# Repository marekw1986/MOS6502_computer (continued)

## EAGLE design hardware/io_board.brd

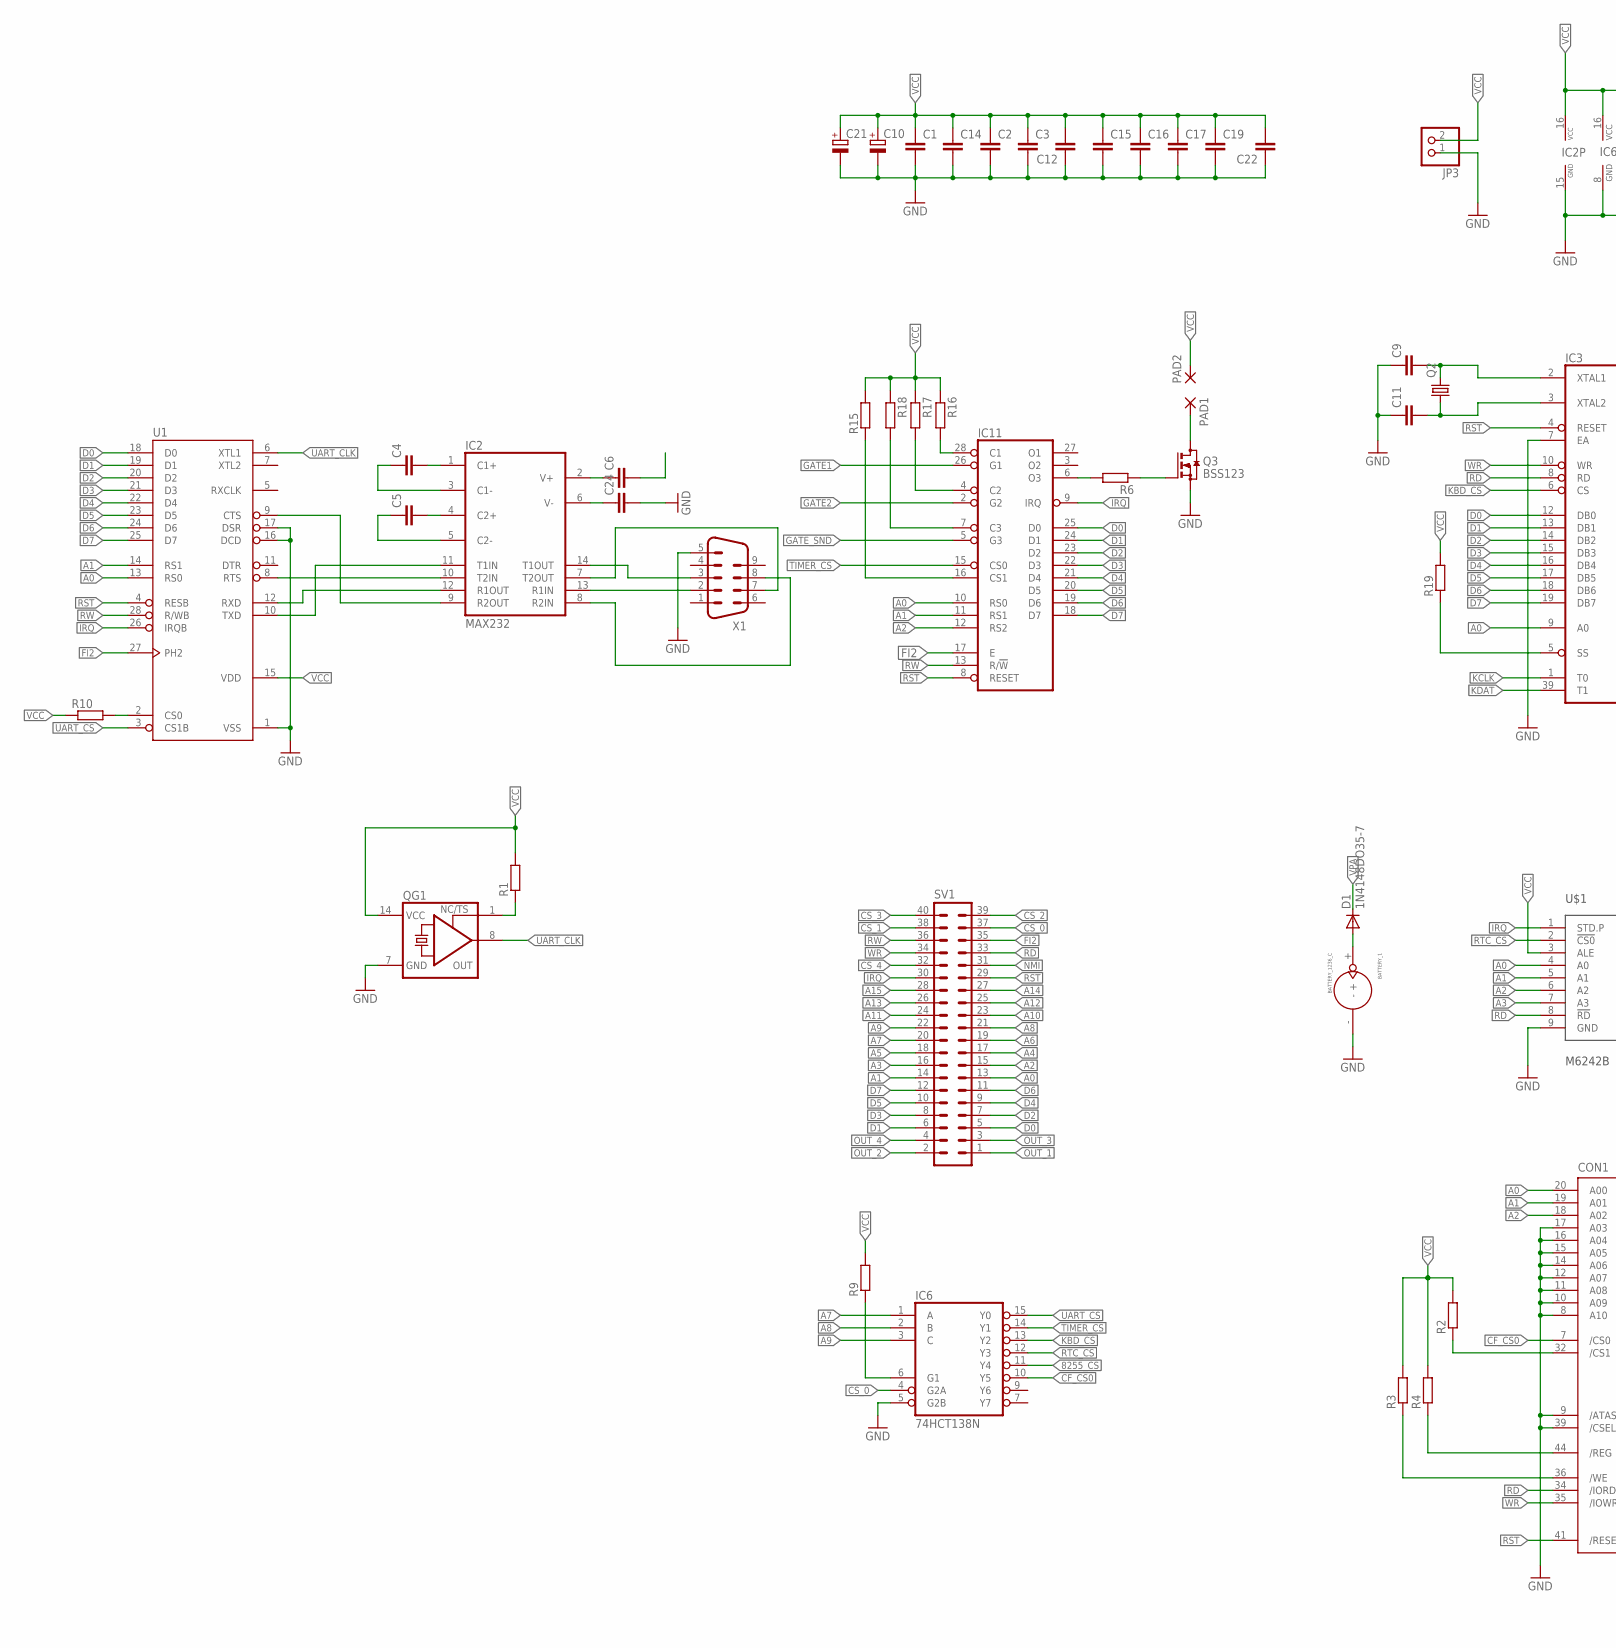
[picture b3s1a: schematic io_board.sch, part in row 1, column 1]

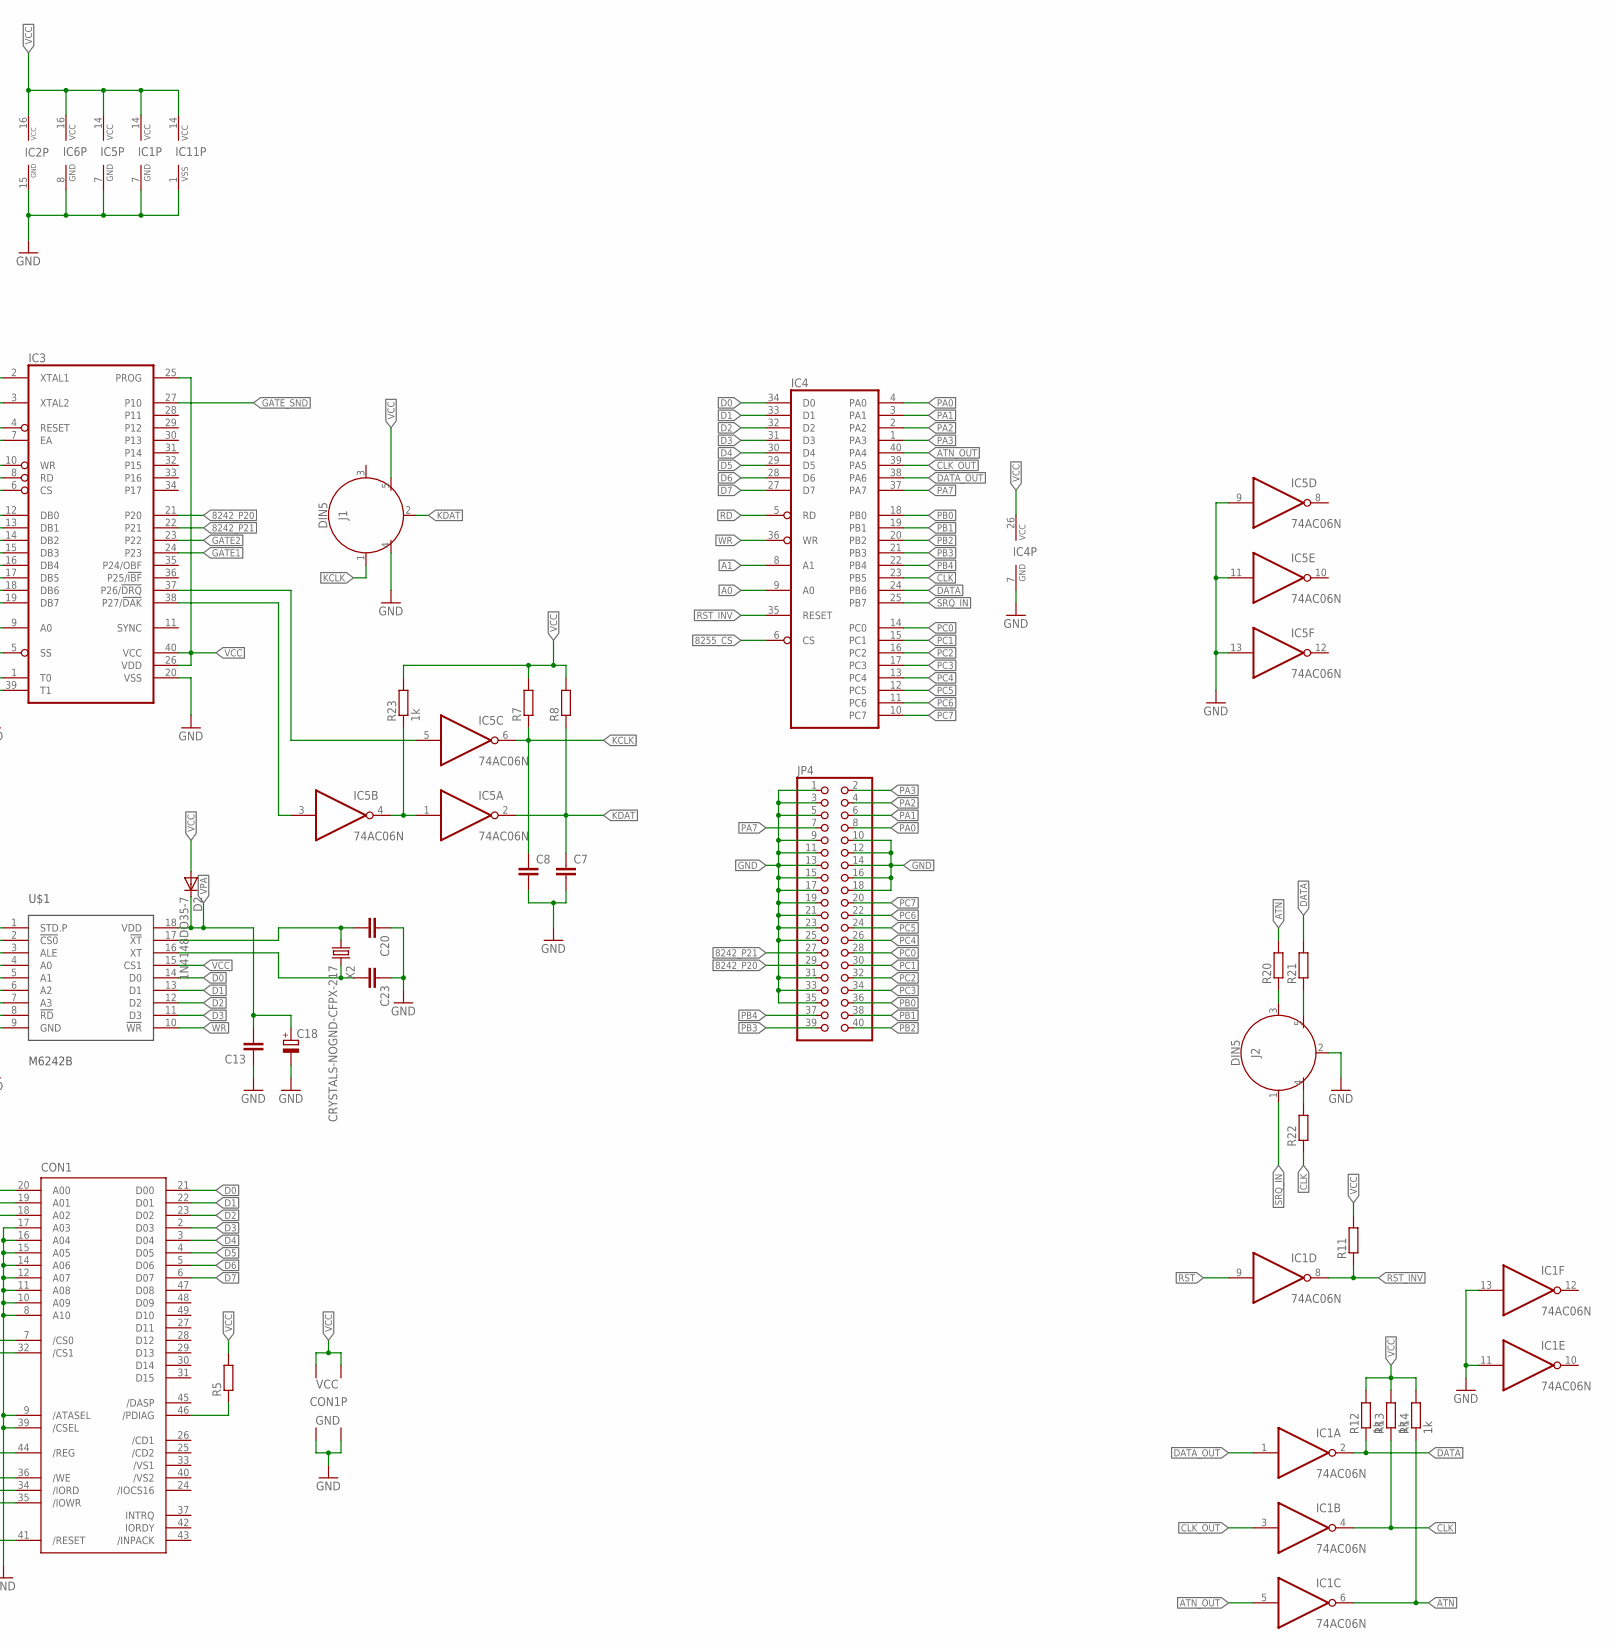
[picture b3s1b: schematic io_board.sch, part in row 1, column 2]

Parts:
BATTERY_1: BATTERY_1236_C
C1, C2, C3, C14, C15, C16, C17: C-EUC1206; C1206
C4, C5, C6, C7, C8, C9, C11, C12, C13, C19, C20, C22, C23, C24: C-EUC0603; C0603
C10: CPOL-EUE5-10.5; E5-10,5
C18, C21: CPOL-EUSMCB; SMC_B
CON1: CF-CARD-IDE_MODE; MI20-50PD-SF
D1, D2: 1N4148DO35-7; DO35-7
IC1, IC5: 74AC06N; DIL14
IC2: MAX232; DIL16
IC3: UPI-8042AH; DIL40
IC4: 8255A; DIL40
IC6: 74HCT138N; DIL16
IC11: 6840; DIL28
J1, J2: DIN5; DIN5-RA-PTH
JP3: PINHD-1X2/90; 1X02/90
JP4: PINHD-2X20; 2X20
PAD1, PAD2: 2,15/1,0
Q2: CRYSTALHC49S; HC49/S
Q3: BSS123; SOT23
QG1: XO-14; DIL14S
R1, R9: R-EU_R1206; R1206
R2, R3, R4, R5, R6, R7, R8, R10, R11, R15, R17, R18: R-EU_R0603; R0603
R12, R14, R23: 1k; 0204/7
R13: 1k; 0204/5
R16, R19: R-EU_0204/5; 0204/5
R20, R21, R22: R-EU_R0805; R0805
SV1: ML40L
U1: G65SC51P; DIP-28
U$1: M6242B; DIL18
X1: M09HP
X2: CRYSTALS-NOGND-CFPX-217; 3.2X1.5-2-PAD

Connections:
8242_P20: IC3.21 (P20), JP4.29
8242_P21: IC3.22 (P21), JP4.27
8255_CS: IC4.6 (CS), IC6.11 (Y4)
A0: CON1.20 (A00), IC3.9 (A0), IC4.9 (A0), IC11.10 (RS0), SV1.13, U1.13 (RS0), U$1.4 (A0)
A1: CON1.19 (A01), IC4.8 (A1), IC11.11 (RS1), SV1.14, U1.14 (RS1), U$1.5 (A1)
A2: CON1.18 (A02), IC11.12 (RS2), SV1.15, U$1.6 (A2)
A3: SV1.16, U$1.7 (A3)
A4: SV1.17
A5: SV1.18
A6: SV1.19
A7: IC6.1 (A), SV1.20
A8: IC6.2 (B), SV1.21
A9: IC6.3 (C), SV1.22
A10: SV1.23
A11: SV1.24
A12: SV1.25
A13: SV1.26
A14: SV1.27
A15: SV1.28
ATN: IC1.6 (O), R14.1, R20.2
ATN_OUT: IC1.5 (I), IC4.40 (PA4)
CF_CS0: CON1.7 (/CS0), IC6.10 (Y5)
CLK: IC1.4 (O), IC4.23 (PB5), R13.1, R22.1
CLK_OUT: IC1.3 (I), IC4.39 (PA5)
CS_0: IC6.4 (G2A), SV1.37
CS_1: SV1.38
CS_2: SV1.39
CS_3: SV1.40
CS_4: SV1.32
CTS_RS232: IC2.8 (R2IN), X1.8
CTS_TTL: IC2.9 (R2OUT), U1.9 (CTS)
D0: CON1.21 (D00), IC3.12 (DB0), IC4.34 (D0), IC11.25 (D0), SV1.5, U1.18 (D0), U$1.14 (D0)
D1: CON1.22 (D01), IC3.13 (DB1), IC4.33 (D1), IC11.24 (D1), SV1.6, U1.19 (D1), U$1.13 (D1)
D2: CON1.23 (D02), IC3.14 (DB2), IC4.32 (D2), IC11.23 (D2), SV1.7, U1.20 (D2), U$1.12 (D2)
D3: CON1.2 (D03), IC3.15 (DB3), IC4.31 (D3), IC11.22 (D3), SV1.8, U1.21 (D3), U$1.11 (D3)
D4: CON1.3 (D04), IC3.16 (DB4), IC4.30 (D4), IC11.21 (D4), SV1.9, U1.22 (D4)
D5: CON1.4 (D05), IC3.17 (DB5), IC4.29 (D5), IC11.20 (D5), SV1.10, U1.23 (D5)
D6: CON1.5 (D06), IC3.18 (DB6), IC4.28 (D6), IC11.19 (D6), SV1.11, U1.24 (D6)
D7: CON1.6 (D07), IC3.19 (DB7), IC4.27 (D7), IC11.18 (D7), SV1.12, U1.25 (D7)
DATA: IC1.2 (O), IC4.24 (PB6), R12.1, R21.2
DATA_OUT: IC1.1 (I), IC4.38 (PA6)
FI2: IC11.17 (E), SV1.35, U1.27 (PH2)
GATE1: IC3.24 (P23), IC11.26 (G1)
GATE2: IC3.23 (P22), IC11.2 (G2)
GATE_SND: IC3.27 (P10), IC11.5 (G3)
GND: BATTERY_1.-, C1.2, C2.2, C3.2, C7.2, C8.2, C9.1, C10.-, C11.1, C12.1, C13.1, C14.2, C15.2, C16.2, C17.2, C18.-, C19.2, C20.1, C21.-, C22.1, C23.1, C24.2, CON1.1 (GND1), CON1.8 (A10), CON1.9 (/ATASEL), CON1.10 (A09), CON1.11 (A08), CON1.12 (A07), CON1.14 (A06), CON1.15 (A05), CON1.16 (A04), CON1.17 (A03), CON1.39 (/CSEL), CON1.50 (GND2), IC1.7 (GND), IC1.11 (I), IC1.13 (I), IC2.15 (GND), IC3.7 (EA), IC3.20 (VSS), IC4.7 (GND), IC5.7 (GND), IC5.9 (I), IC5.11 (I), IC5.13 (I), IC6.5 (G2B), IC6.8 (GND), IC11.1 (VSS), J1.4, J2.2, JP3.1, JP4.1, JP4.3, JP4.5, JP4.9, JP4.10, JP4.11, JP4.12, JP4.13, JP4.14, JP4.15, JP4.16, JP4.17, JP4.18, JP4.19, JP4.21, JP4.23, JP4.25, JP4.31, JP4.33, JP4.35, Q3.2 (S), QG1.7 (GND), U1.1 (VSS), U1.16 (DCD), U1.17 (DSR), U$1.9 (GND), X1.5
IRQ: IC11.9 (IRQ), SV1.30, U1.26 (IRQB), U$1.1 (STD.P)
KBD_CS: IC3.6 (CS), IC6.13 (Y2)
KCLK: C8.1, IC3.1 (T0), IC5.6 (O), J1.1, R7.1
KDAT: C7.1, IC3.39 (T1), IC5.2 (O), J1.2, R8.1
unnamed: C24.1, IC2.6 (V-)
unnamed: IC3.38 (P27/!DAK), IC5.3 (I)
unnamed: QG1.1 (TS), R1.1
unnamed: C4.2, IC2.1 (C1+)
unnamed: C5.2, IC2.4 (C2+)
unnamed: C5.1, IC2.5 (C2-)
unnamed: C4.1, IC2.3 (C1-)
unnamed: C6.1, IC2.2 (V+)
unnamed: C9.2, IC3.2 (XTAL1), Q2.2
unnamed: C11.2, IC3.3 (XTAL2), Q2.1
unnamed: IC3.37 (P26/!DRQ), IC5.5 (I)
unnamed: IC6.6 (G1), R9.1
unnamed: CON1.44 (/REG), R4.1
unnamed: CON1.36 (/WE), R3.1
unnamed: CON1.46 (/PDIAG), R5.1
unnamed: BATTERY_1.+, D1.A
unnamed: PAD1.1, Q3.3 (D)
unnamed: R10.2, U1.2 (CS0)
unnamed: CON1.32 (/CS1), R2.1
unnamed: IC11.6 (O3), R6.2
unnamed: IC11.16 (CS1), R15.1
unnamed: IC11.28 (C1), R16.2
unnamed: IC11.4 (C2), R17.2
unnamed: IC11.7 (C3), R18.2
unnamed: IC3.5 (SS), R19.1
unnamed: J2.3, R20.1
unnamed: J2.5, R21.1
unnamed: J2.4, R22.2
unnamed: IC5.1 (I), IC5.4 (O), R23.1
NMI: SV1.31
OUT_1: SV1.1
OUT_2: SV1.2
OUT_3: SV1.3
OUT_4: SV1.4
PA0: IC4.4 (PA0), JP4.8
PA1: IC4.3 (PA1), JP4.6
PA2: IC4.2 (PA2), JP4.4
PA3: IC4.1 (PA3), JP4.2
PA7: IC4.37 (PA7), JP4.7
PB0: IC4.18 (PB0), JP4.36
PB1: IC4.19 (PB1), JP4.38
PB2: IC4.20 (PB2), JP4.40
PB3: IC4.21 (PB3), JP4.39
PB4: IC4.22 (PB4), JP4.37
PC0: IC4.14 (PC0), JP4.28
PC1: IC4.15 (PC1), JP4.30
PC2: IC4.16 (PC2), JP4.32
PC3: IC4.17 (PC3), JP4.34
PC4: IC4.13 (PC4), JP4.26
PC5: IC4.12 (PC5), JP4.24
PC6: IC4.11 (PC6), JP4.22
PC7: IC4.10 (PC7), JP4.20
RD: CON1.34 (/IORD), IC3.8 (RD), IC4.5 (RD), SV1.33, U$1.8 (!RD)
RST: CON1.41 (/RESET), IC1.9 (I), IC3.4 (RESET), IC11.8 (RESET), SV1.29, U1.4 (RESB)
RST_INV: IC1.8 (O), IC4.35 (RESET), R11.1
RTC_CS: IC6.12 (Y3), U$1.2 (!CS0)
RTS_RS232: IC2.7 (T2OUT), X1.7
RTS_TTL: IC2.10 (T2IN), U1.8 (RTS)
RW: IC11.13 (R/!W), SV1.36, U1.28 (R/WB)
RXD_RS232: IC2.13 (R1IN), X1.2
RXD_TTL: IC2.12 (R1OUT), U1.12 (RXD)
SND_PULSE: Q3.1 (G), R6.1
SOSCI: C20.2, U$1.17 (!XT), X2.1
SOSCO: C23.2, U$1.16 (XT), X2.2
SRQ_IN: IC4.25 (PB7), J2.1
TIMER_CS: IC6.14 (Y1), IC11.15 (CS0)
TXD_RS232: IC2.14 (T1OUT), X1.3
TXD_TTL: IC2.11 (T1IN), U1.10 (TXD)
UART_CLK: QG1.8 (OUT), U1.6 (XTL1)
UART_CS: IC6.15 (Y0), U1.3 (CS1B)
VCC: C1.1, C2.1, C3.1, C6.2, C10.+, C12.2, C14.1, C15.1, C16.1, C17.1, C19.1, C21.+, C22.2, CON1.13 (VCC2), CON1.38 (VCC1), D2.A, IC1.14 (VCC), IC2.16 (VCC), IC3.25 (PROG), IC3.26 (VDD), IC3.40 (VCC), IC4.26 (VCC), IC5.14 (VCC), IC6.16 (VCC), IC11.14 (VCC), J1.5, JP3.2, PAD2.1, QG1.14 (VCC), R1.2, R2.2, R3.2, R4.2, R5.2, R7.2, R8.2, R9.2, R10.1, R11.2, R12.2, R13.2, R14.2, R15.2, R16.1, R17.1, R18.1, R19.2, R23.2, U1.15 (VDD), U$1.3 (ALE), U$1.15 (CS1)
VPA: C13.2, C18.+, D1.C, D2.C, U$1.18 (VDD)
WR: CON1.35 (/IOWR), IC3.10 (WR), IC4.36 (WR), SV1.34, U$1.10 (!WR)

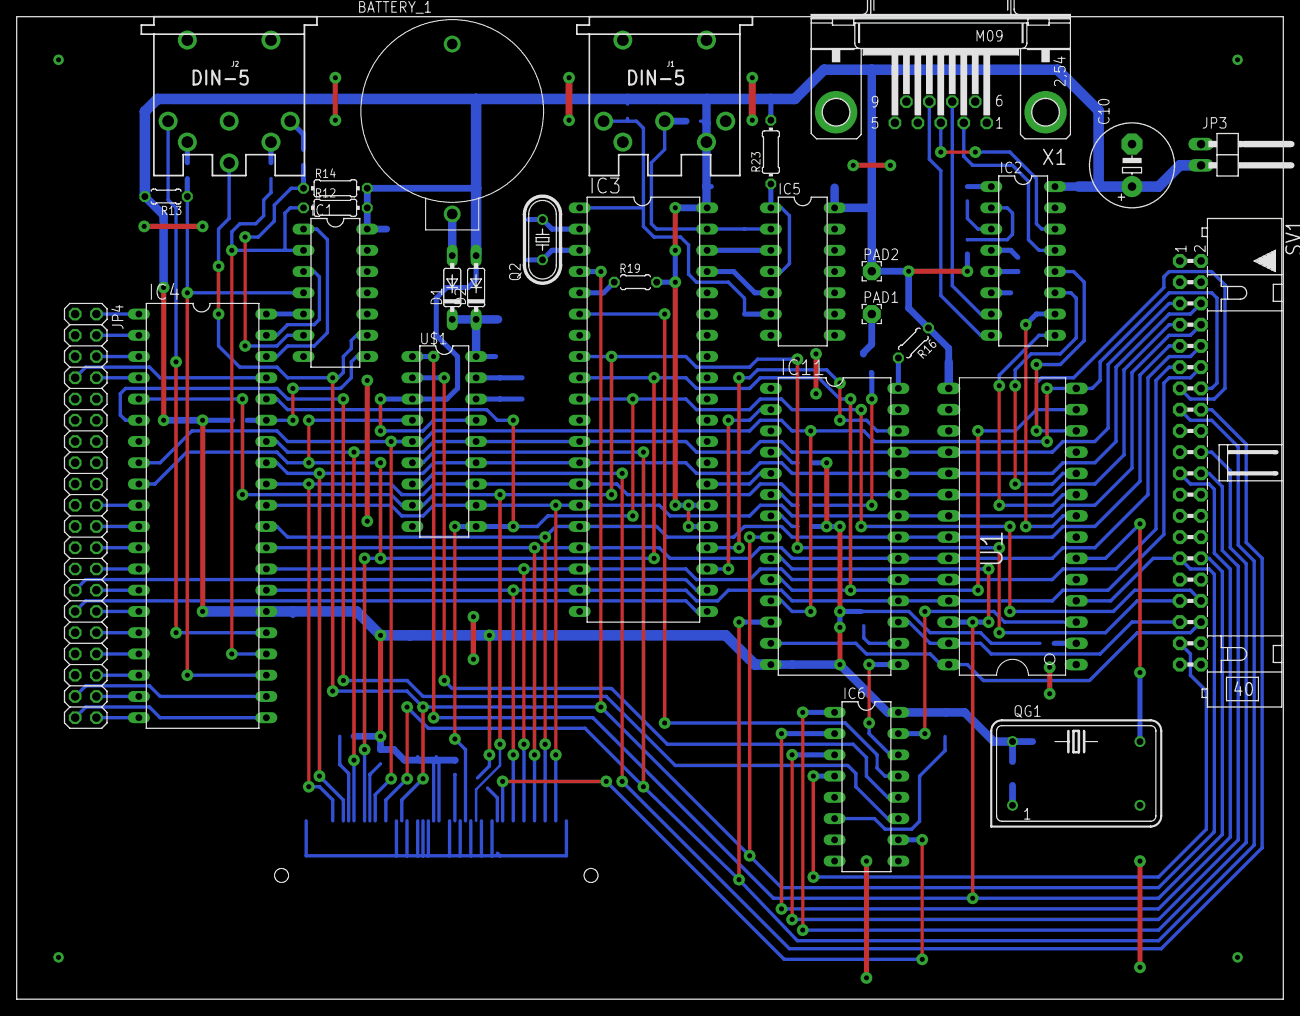
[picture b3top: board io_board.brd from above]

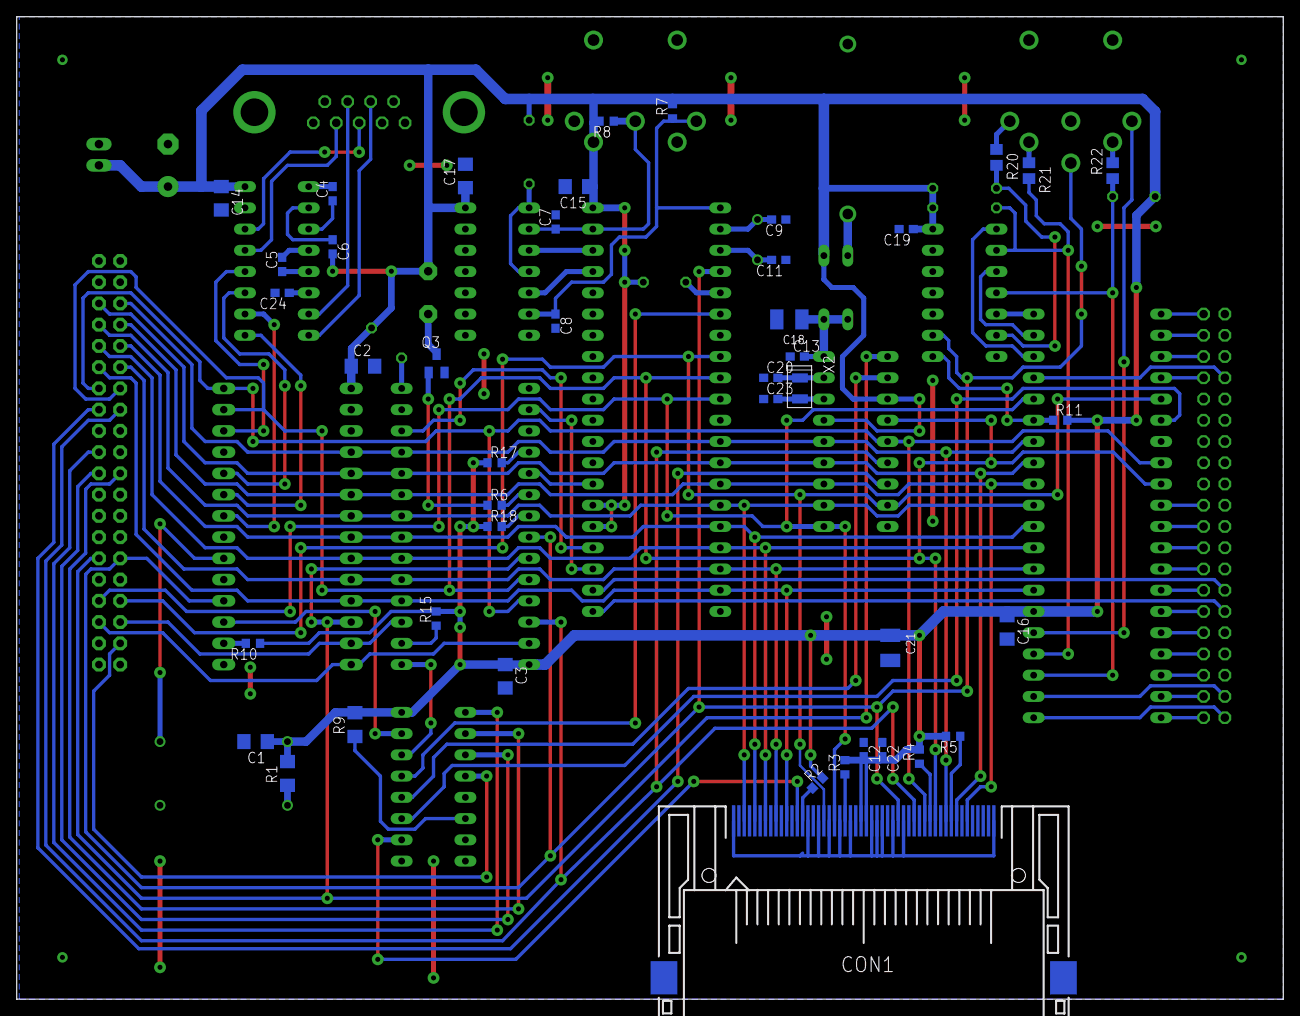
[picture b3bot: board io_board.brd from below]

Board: 2 copper layers, 151.4 x 117.5 mm, 72 parts (43 on the bottom side), 105 nets.

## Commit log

2021-03-12 gitignore
2021-07-25 VDP test
2021-07-30 CRT controller works
2021-07-30 Screen terminal test
2021-07-30 Terminal screen update
2021-08-01 Screen terminal fixes
2021-08-02 Scrolling
2021-08-02 Screen scrolling
2021-08-02 Newline
2021-08-02 Some changes
2021-08-03 Backspace added
2021-08-25 PCB update
2024-05-11 Better fonts added
2026-06-23 Experiments with file system
2026-06-24 ROM snapshot added
2026-06-24 Fixes
2026-06-24 New fonts added
2026-06-24 Fix. Code compiles.
2026-06-24 Bug fix: computer boots without UART connected
2026-06-24 Test version of simple flat FS added
2026-06-25 Keyboard routines modified to support Ctrl key combinations
2026-06-25 Shift/Ctrl handling error fixed
2026-06-25 fs.asm updated
2026-06-25 CF FS experimental code removed due to instability. Possibly caused by hardware - lack of buffer on data bus. Old ACIA names removed from min_mon.
